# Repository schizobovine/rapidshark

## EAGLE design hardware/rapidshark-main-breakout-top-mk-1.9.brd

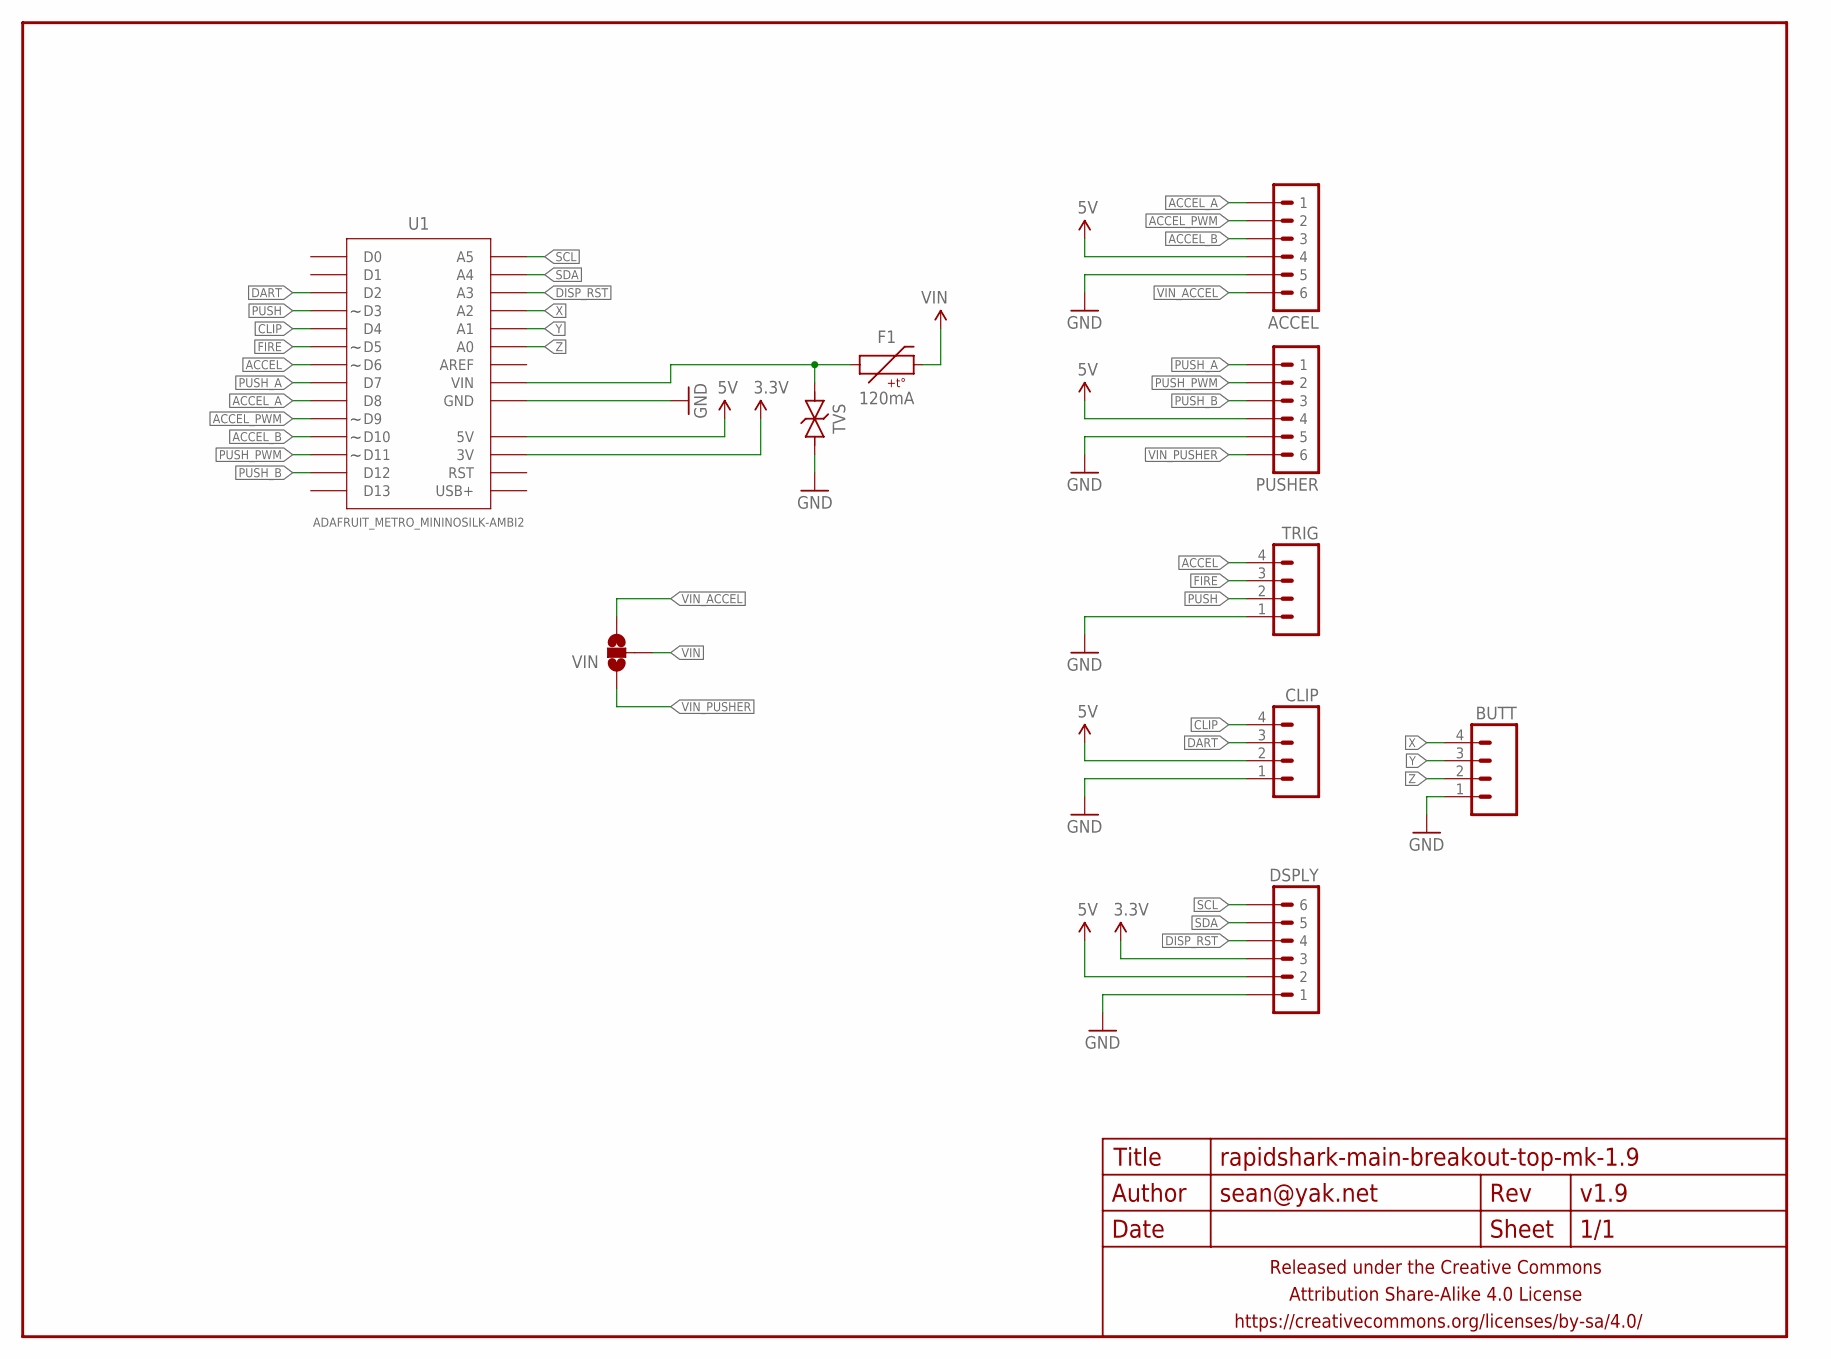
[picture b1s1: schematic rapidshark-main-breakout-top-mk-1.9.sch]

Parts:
ACCEL: M06JST-PH-PTH-VERT; JST-6-PH-VERT-PTH
BUTT: M04JST-PTH-VERT; JST-4-PH-VERT-PTH
CLIP: M04JST-PTH-VERT; JST-4-PH-VERT-PTH
DSPLY: M06JST-PH-PTH-VERT; JST-6-PH-VERT-PTH
F1: 120mA; PTC-1206
FRAME1: FRAME-LETTERNO_PACKAGE; DUMMY
PUSHER: M06JST-PH-PTH-VERT; JST-6-PH-VERT-PTH
TRIG: M04JST-PTH-VERT; JST-4-PH-VERT-PTH
TVS: TVSSMA; SMA-DIODE-TVS-BIDIR
U1: ADAFRUIT_METRO_MININOSILK-AMBI2; ADAFRUIT_METRO_MINI_BACK
VIN: JUMPER-PAD-3-NOFULL_BOX_SILK; PAD-JUMPER-3-NO_YES_SILK_FULL_BOX

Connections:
3.3V: DSPLY.3, U1.17 (3V)
5V: ACCEL.4, CLIP.2, DSPLY.2, PUSHER.4, U1.18 (5V)
ACCEL: TRIG.4, U1.7 (D6)
ACCEL_A: ACCEL.1, U1.9 (D8)
ACCEL_B: ACCEL.3, U1.11 (D10)
ACCEL_PWM: ACCEL.2, U1.10 (D9)
CLIP: CLIP.4, U1.5 (D4)
DART: CLIP.3, U1.3 (D2)
DISP_RST: DSPLY.4, U1.26 (A3)
FIRE: TRIG.3, U1.6 (D5)
GND: ACCEL.5, BUTT.1, CLIP.1, DSPLY.1, PUSHER.5, TRIG.1, TVS.1, U1.19 (GND), U1.20 (GND)
unnamed: F1.1, TVS.2, U1.21 (VIN)
PUSH: TRIG.2, U1.4 (D3)
PUSH_A: PUSHER.1, U1.8 (D7)
PUSH_B: PUSHER.3, U1.13 (D12)
PUSH_PWM: PUSHER.2, U1.12 (D11)
SCL: DSPLY.6, U1.28 (A5)
SDA: DSPLY.5, U1.27 (A4)
VIN: F1.2, VIN.2
VIN_ACCEL: ACCEL.6, VIN.3
VIN_PUSHER: PUSHER.6, VIN.1
X: BUTT.4, U1.25 (A2)
Y: BUTT.3, U1.24 (A1)
Z: BUTT.2, U1.23 (A0)

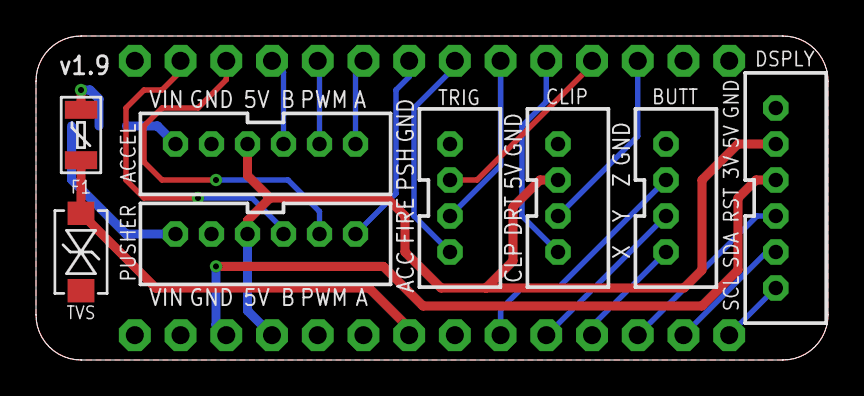
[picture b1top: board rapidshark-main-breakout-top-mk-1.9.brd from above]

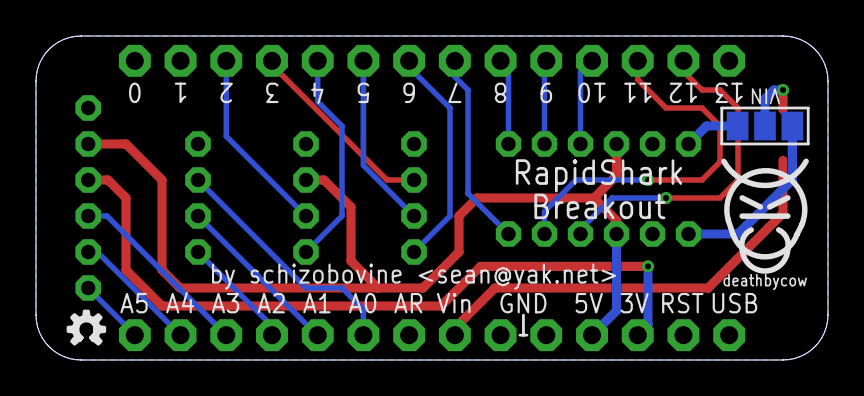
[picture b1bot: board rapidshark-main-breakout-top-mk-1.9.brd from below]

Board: 2 copper layers, 44.0 x 18.0 mm, 13 parts (4 on the bottom side), 24 nets.

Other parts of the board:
U$2: COW_SMALL
U$3: OSHWLOGO_TINY_SILKONLY

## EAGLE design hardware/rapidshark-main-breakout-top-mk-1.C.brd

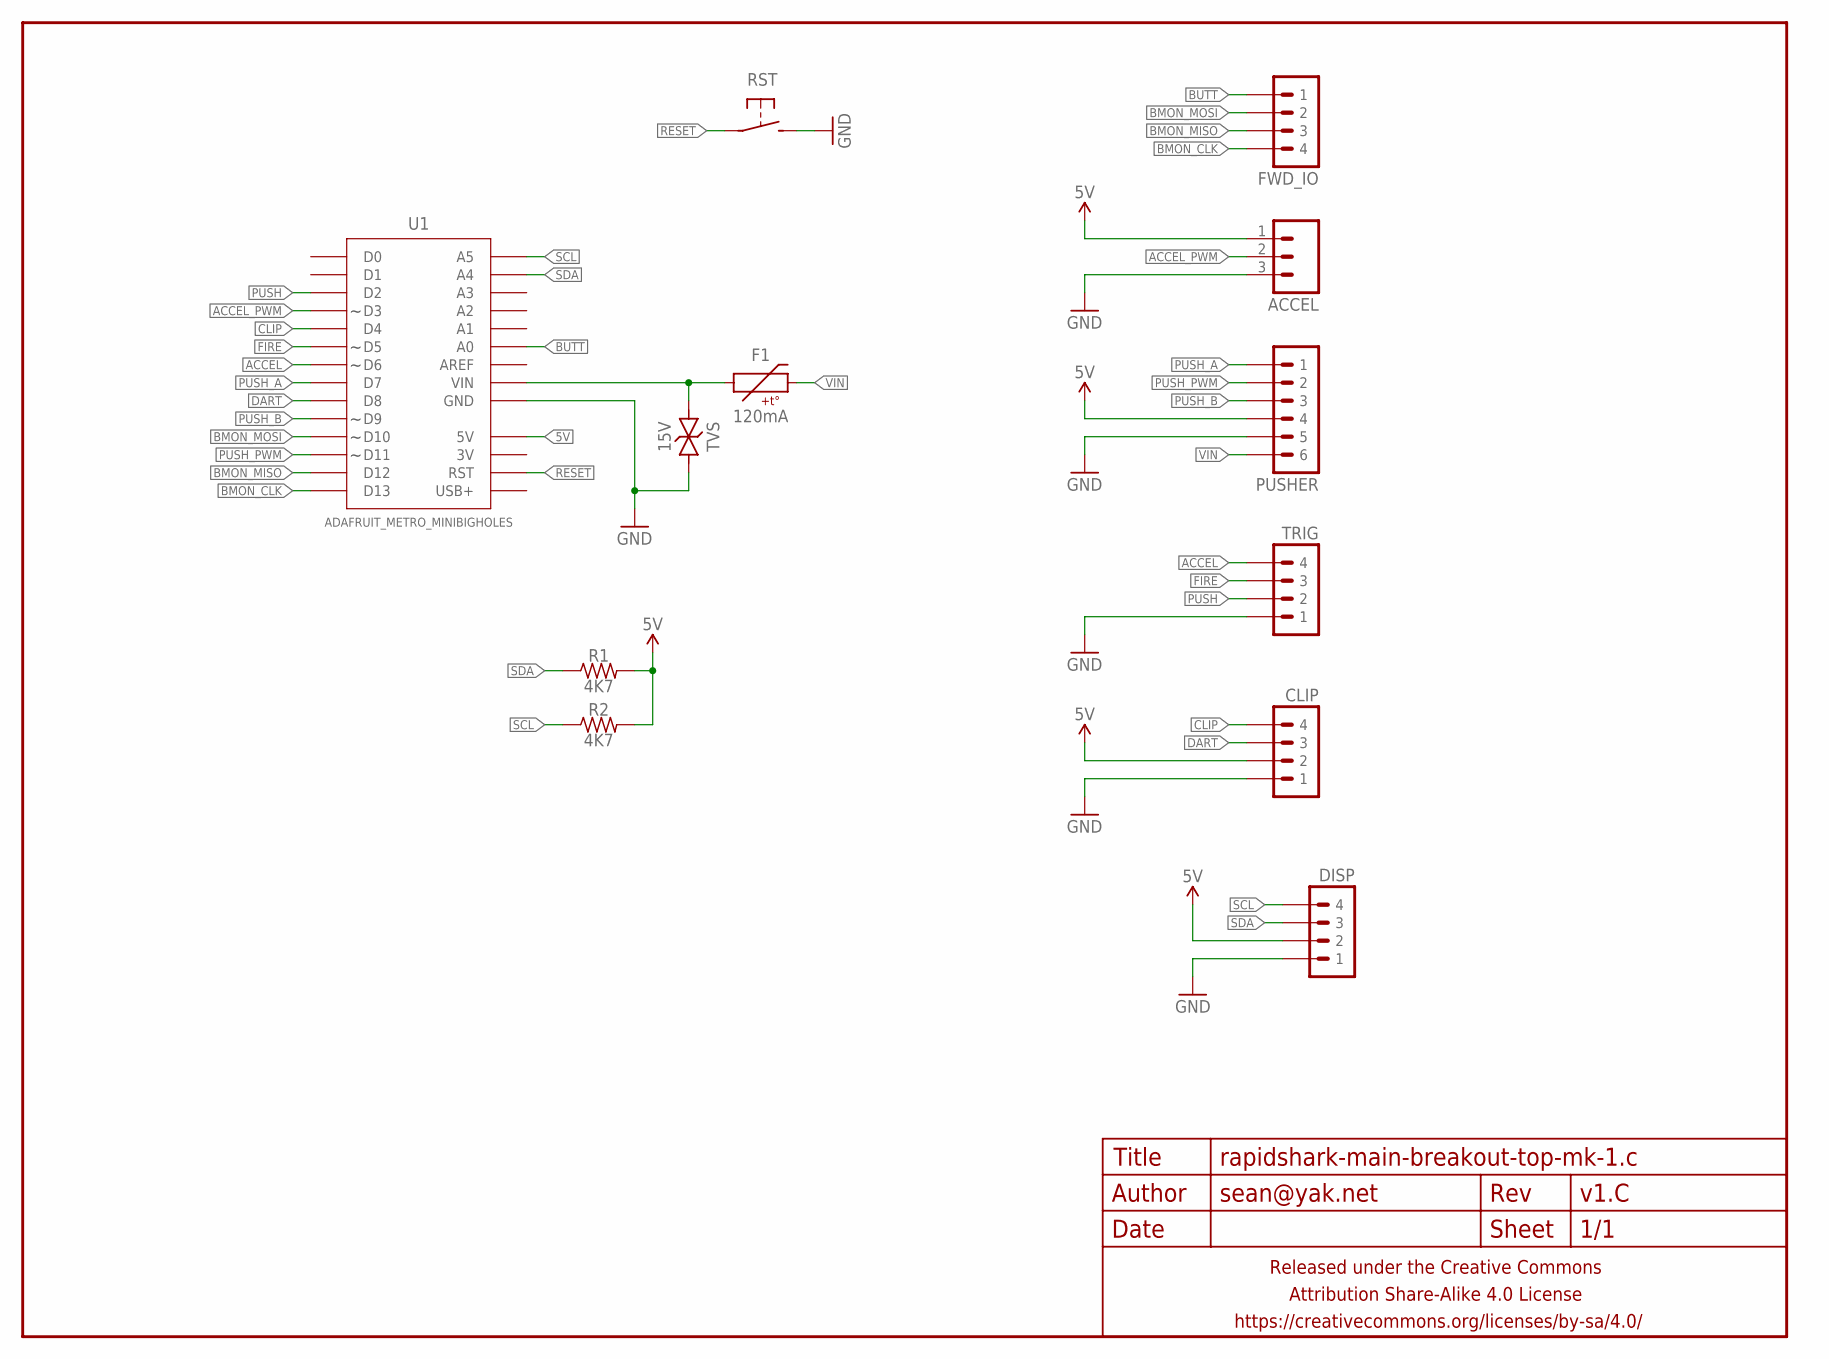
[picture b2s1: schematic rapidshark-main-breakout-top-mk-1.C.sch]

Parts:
ACCEL: M03JST-PTH-VERT-CENTERED; JST-3-PH-VERT-PTH-CENTERED
CLIP: M04JST-PTH-VERT; JST-4-PH-VERT-PTH
DISP: M04JST-PTH-VERT; JST-4-PH-VERT-PTH
F1: 120mA; PTC-1206
FRAME1: FRAME-LETTERNO_PACKAGE; DUMMY
FWD_IO: M04JST-PTH-VERT; JST-4-PH-VERT-PTH
PUSHER: M06JST-PH-PTH-VERT; JST-6-PH-VERT-PTH
R1, R2: 4K7; R0603-TIGHTER
RST: SPST-NO-TACTCK-PTS840-GK; TACTILE-SMD-CK-PTS840-GK
TRIG: M04JST-PTH-VERT; JST-4-PH-VERT-PTH
TVS: 15V; SMA-DIODE-TVS-BIDIR
U1: ADAFRUIT_METRO_MINIBIGHOLES; ADAFRUIT_METRO_MINI_BIGHOLES

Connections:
5V: ACCEL.1, CLIP.2, DISP.2, PUSHER.4, R1.2, R2.2, U1.18 (5V)
ACCEL: TRIG.4, U1.7 (D6)
ACCEL_PWM: ACCEL.2, U1.4 (D3)
BMON_CLK: FWD_IO.4, U1.14 (D13)
BMON_MISO: FWD_IO.3, U1.13 (D12)
BMON_MOSI: FWD_IO.2, U1.11 (D10)
BUTT: FWD_IO.1, U1.23 (A0)
CLIP: CLIP.4, U1.5 (D4)
DART: CLIP.3, U1.9 (D8)
FIRE: TRIG.3, U1.6 (D5)
GND: ACCEL.3, CLIP.1, DISP.1, PUSHER.5, RST.3 (2), RST.4 (2), TRIG.1, TVS.1, U1.19 (GND), U1.20 (GND)
unnamed: F1.1, TVS.2, U1.21 (VIN)
PUSH: TRIG.2, U1.3 (D2)
PUSH_A: PUSHER.1, U1.8 (D7)
PUSH_B: PUSHER.3, U1.10 (D9)
PUSH_PWM: PUSHER.2, U1.12 (D11)
RESET: RST.1, RST.2 (1), U1.16 (RST)
SCL: DISP.4, R2.1, U1.28 (A5)
SDA: DISP.3, R1.1, U1.27 (A4)
VIN: F1.2, PUSHER.6

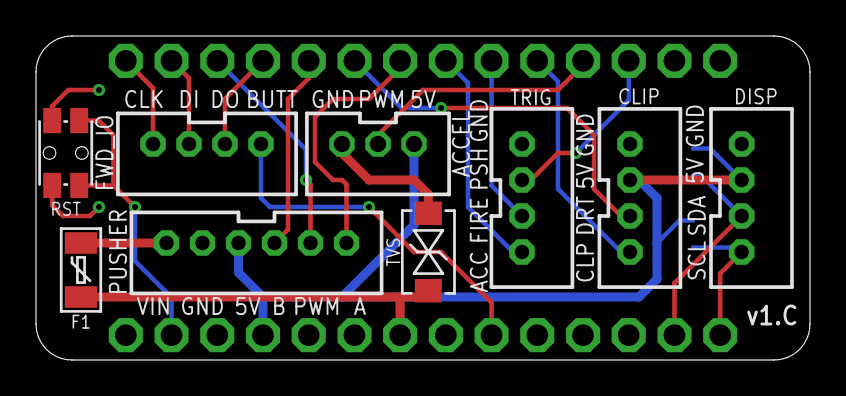
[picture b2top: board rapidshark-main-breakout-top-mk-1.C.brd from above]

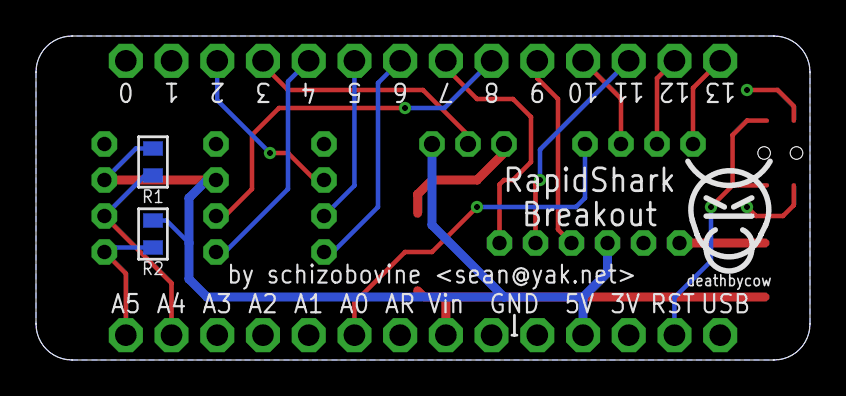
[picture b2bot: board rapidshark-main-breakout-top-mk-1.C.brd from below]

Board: 2 copper layers, 43.0 x 18.0 mm, 14 parts (4 on the bottom side), 20 nets.

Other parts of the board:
U$2: COW_SMALL

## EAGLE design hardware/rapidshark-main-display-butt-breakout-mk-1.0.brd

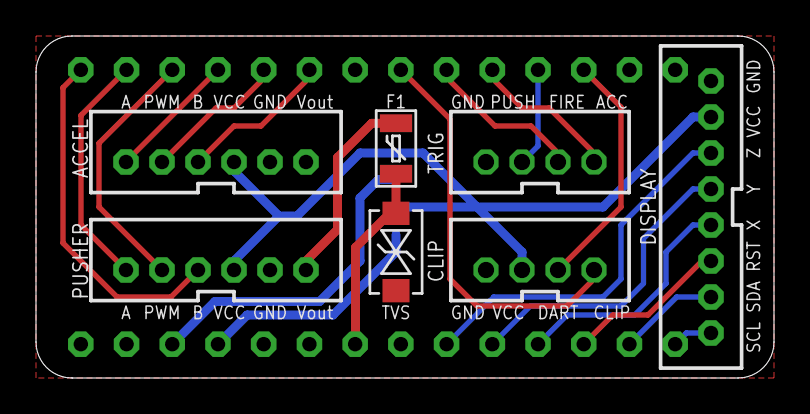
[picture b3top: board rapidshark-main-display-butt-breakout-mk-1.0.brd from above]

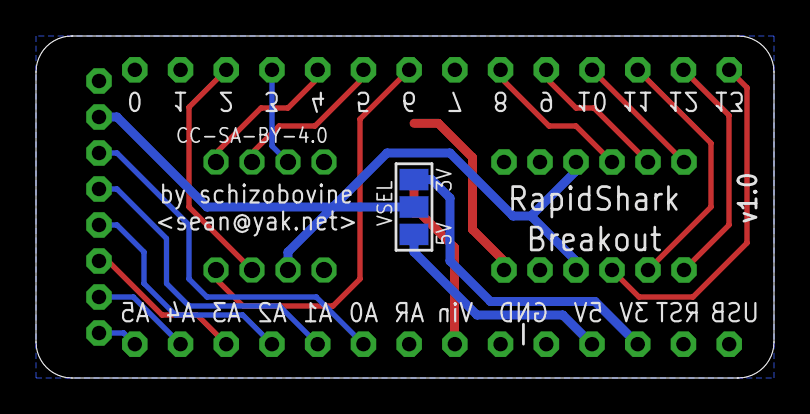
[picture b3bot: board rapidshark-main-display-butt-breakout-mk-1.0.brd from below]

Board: 2 copper layers, 41.0 x 19.0 mm, 10 parts (2 on the bottom side), 23 nets.

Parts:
ACCEL: M06JST-PH-PTH-VERT; JST-6-PH-VERT-PTH
CLIP: M04JST-PTH-VERT; JST-4-PH-VERT-PTH
DISPLAY: JST-8-VERT-PTH
F1: 100mA; PTC-1206
FRAME1: FRAME-LETTERNO_PACKAGE; DUMMY
PUSHER: M06JST-PH-PTH-VERT; JST-6-PH-VERT-PTH
TRIG: M04JST-PTH-VERT; JST-4-PH-VERT-PTH
TVS: SMA-DIODE-TVS-BIDIR
U1: ADAFRUIT_METRO_MINI_BACK
VSEL: PAD-JUMPER-3-NO_YES_SILK_FULL_BOX

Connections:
3.3V: U1.17, VSEL.1
5V: U1.18, VSEL.3
ACCEL: TRIG.4, U1.5
ACCEL_A: ACCEL.1, U1.11
ACCEL_B: ACCEL.3, U1.9
ACCEL_PWM: ACCEL.2, U1.10
CLIP: CLIP.4, U1.7
DART: CLIP.3, U1.3
DISP_RST: DISPLAY.3, U1.26
FIRE: TRIG.3, U1.6
GND: ACCEL.5, CLIP.1, DISPLAY.8, PUSHER.5, TRIG.1, TVS.1, U1.19, U1.20
unnamed: F1.1, TVS.2, U1.21
PUSH: TRIG.2, U1.4
PUSH_A: PUSHER.1, U1.13
PUSH_B: PUSHER.3, U1.14
PUSH_PWM: PUSHER.2, U1.12
SCL: DISPLAY.1, U1.28
SDA: DISPLAY.2, U1.27
VCC: ACCEL.4, CLIP.2, DISPLAY.7, PUSHER.4, VSEL.2
VIN: F1.2, PUSHER.6
X: DISPLAY.4, U1.25
Y: DISPLAY.5, U1.24
Z: DISPLAY.6, U1.23

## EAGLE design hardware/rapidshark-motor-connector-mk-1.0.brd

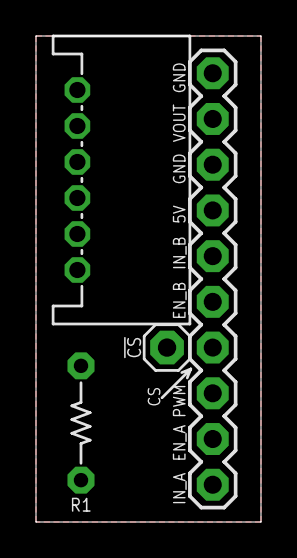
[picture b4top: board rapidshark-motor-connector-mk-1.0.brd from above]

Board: 2 copper layers, 12.5 x 27.0 mm, 5 parts (1 on the bottom side), 7 nets, no tracks yet.

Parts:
!CS: M01PTH; 1X01
FRAME1: FRAME-LETTERNO_PACKAGE; DUMMY
JP1: M10PTH; 1X10
JP2: M06JST-PH-PTH-RA; JST-6-PH-RA-PTH
R1: 10k; RESISTOR-AXIAL-PTH-6.35MM

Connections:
CS_DIS: !CS.1, R1.P$1
GND: JP1.8, JP1.10, JP2.2
IN_A: JP1.1, JP2.6
IN_B: JP1.6, JP2.4
PWM: JP1.3, JP2.5
VDD: JP1.7, JP2.3, R1.P$2
VOUT: JP1.9, JP2.1

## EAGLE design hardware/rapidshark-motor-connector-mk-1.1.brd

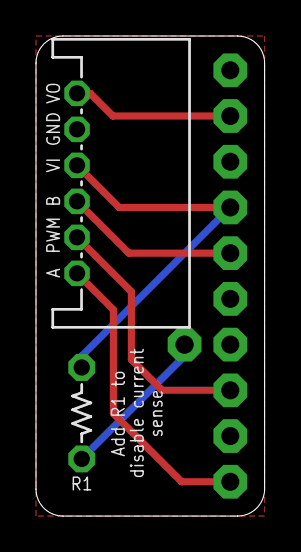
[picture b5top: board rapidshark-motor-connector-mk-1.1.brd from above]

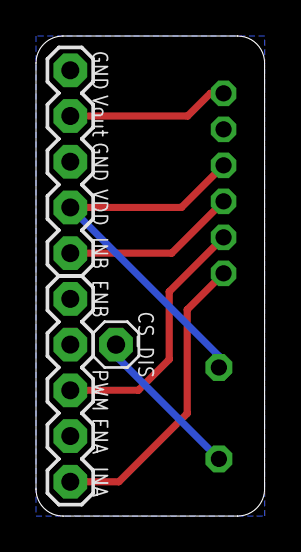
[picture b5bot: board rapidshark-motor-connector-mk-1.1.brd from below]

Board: 2 copper layers, 12.7 x 26.7 mm, 6 parts (4 on the bottom side), 7 nets.

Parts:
!CS: M01PTH; 1X01
FRAME1: FRAME-LETTERNO_PACKAGE; DUMMY
JP1, JP2: M05PTH; 1X05
JP3: M06JST-PH-PTH-RA; JST-6-PH-RA-PTH
R1: 10k; RESISTOR-AXIAL-PTH-5.08MM

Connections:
CS_DIS: !CS.1, R1.P$1
GND: JP1.1, JP1.3, JP3.2
IN_A: JP2.5, JP3.6
IN_B: JP1.5, JP3.4
PWM: JP2.3, JP3.5
VDD: JP1.4, JP3.3, R1.P$2
VOUT: JP1.2, JP3.1

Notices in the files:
parts and their libraries:
A_butts: Released under the Creative Commons Attribution Share-Alike 4.0 License
A_butts: https://creativecommons.org/licenses/by-sa/4.0
A_butts: Released under the Creative Commons
